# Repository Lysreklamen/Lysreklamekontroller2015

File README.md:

# Lysreklamekontroller2015
Modulært design

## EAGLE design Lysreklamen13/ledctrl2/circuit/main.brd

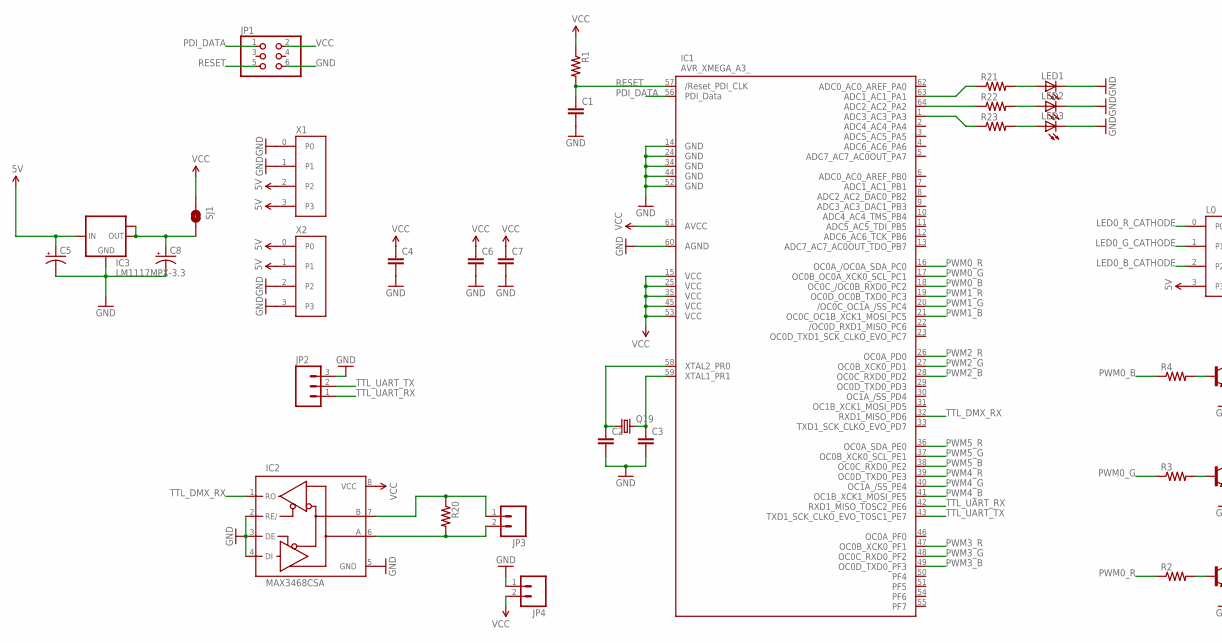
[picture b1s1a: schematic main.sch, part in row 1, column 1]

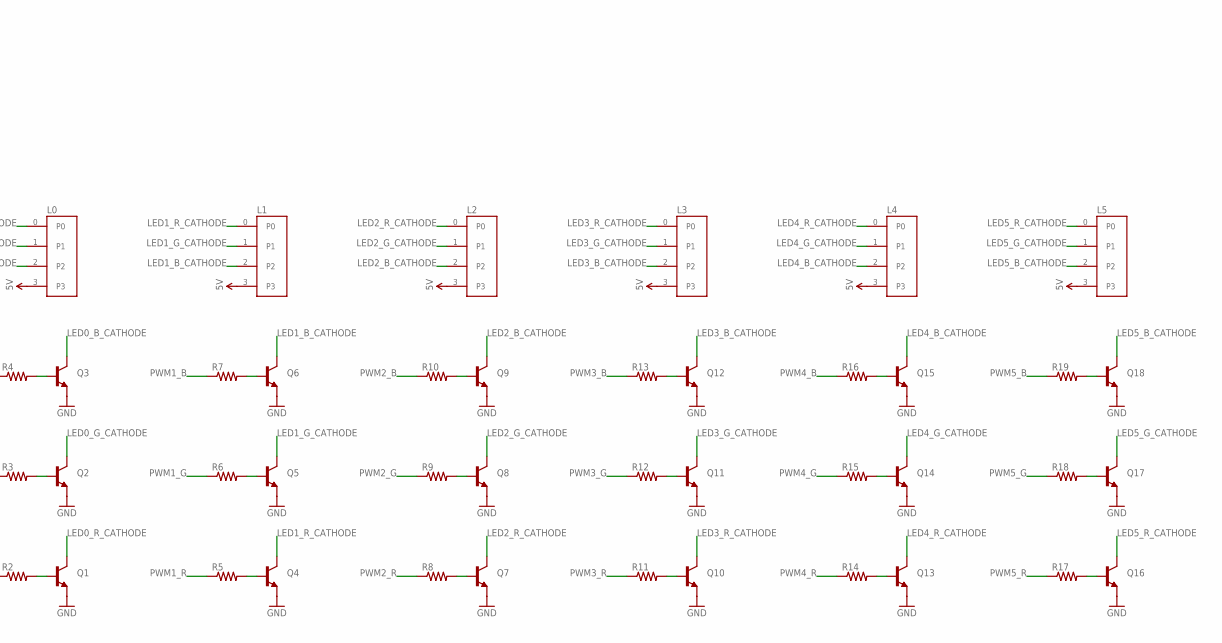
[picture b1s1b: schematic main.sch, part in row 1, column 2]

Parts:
C1, C2, C3, C4, C6, C7: CAP0805; 0805
C5, C8: CAP_POLSMD; VISHAY_C
IC1: AVR_XMEGA_A3_; TQFP64
IC2: MAX3468CSA; SO08
IC3: LM1117MPX-3.3; SOT223
JP1: PINHD-2X3; 2X03
JP2: M03LOCK_LONGPADS; 1X03_LOCK_LONGPADS
JP3, JP4: M02; 1X02_LONGPADS
L0, L1, L2, L3, L4, L5: SCREW-TERMINAL-4P; SK-CZZ-4P
LED1, LED2, LED3: LEDCHIPLED_0805; CHIPLED_0805
Q1, Q2, Q3, Q4, Q5, Q6, Q7, Q8, Q9, Q10, Q11, Q12, Q13, Q14, Q15, Q16, Q17, Q18: TRANSISTOR_NPNSOT89; SOT89
Q19: CRYSTALHC49UP; HC49UP
R1, R2, R3, R4, R5, R6, R7, R8, R9, R10, R11, R12, R13, R14, R15, R16, R17, R18, R19, R20, R21, R22, R23: RESISTOR; 0805
SJ1: SOLDERJUMPERNO; SJ_2S-NO
X1, X2: SCREW-TERMINAL-4P; SK-CZZ-4P

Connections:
5V: C5.+, IC3.3 (IN), L0.3, L1.3, L2.3, L3.3, L4.3, L5.3, X1.2, X1.3, X2.0, X2.1
GND: C1.2, C2.2, C3.2, C4.2, C5.-, C6.2, C7.2, C8.-, IC1.14 (GND1), IC1.24 (GND2), IC1.34 (GND3), IC1.44 (GND4), IC1.52 (GND5), IC1.60 (AGND), IC2.2 (RE/), IC2.3 (DE), IC2.4 (DI), IC2.5 (GND), IC3.1 (GND), JP1.6, JP2.3, JP4.1, LED1.C, LED2.C, LED3.C, Q1.3 (E), Q2.3 (E), Q3.3 (E), Q4.3 (E), Q5.3 (E), Q6.3 (E), Q7.3 (E), Q8.3 (E), Q9.3 (E), Q10.3 (E), Q11.3 (E), Q12.3 (E), Q13.3 (E), Q14.3 (E), Q15.3 (E), Q16.3 (E), Q17.3 (E), Q18.3 (E), X1.0, X1.1, X2.2, X2.3
LED0_B_CATHODE: L0.2, Q3.2 (C)
LED0_G_CATHODE: L0.1, Q2.2 (C)
LED0_R_CATHODE: L0.0, Q1.2 (C)
LED1_B_CATHODE: L1.2, Q6.2 (C)
LED1_G_CATHODE: L1.1, Q5.2 (C)
LED1_R_CATHODE: L1.0, Q4.2 (C)
LED2_B_CATHODE: L2.2, Q9.2 (C)
LED2_G_CATHODE: L2.1, Q8.2 (C)
LED2_R_CATHODE: L2.0, Q7.2 (C)
LED3_B_CATHODE: L3.2, Q12.2 (C)
LED3_G_CATHODE: L3.1, Q11.2 (C)
LED3_R_CATHODE: L3.0, Q10.2 (C)
LED4_B_CATHODE: L4.2, Q15.2 (C)
LED4_G_CATHODE: L4.1, Q14.2 (C)
LED4_R_CATHODE: L4.0, Q13.2 (C)
LED5_B_CATHODE: L5.2, Q18.2 (C)
LED5_G_CATHODE: L5.1, Q17.2 (C)
LED5_R_CATHODE: L5.0, Q16.2 (C)
unnamed: Q1.1 (B), R2.2
unnamed: Q2.1 (B), R3.2
unnamed: Q3.1 (B), R4.2
unnamed: Q4.1 (B), R5.2
unnamed: Q5.1 (B), R6.2
unnamed: Q6.1 (B), R7.2
unnamed: Q7.1 (B), R8.2
unnamed: Q8.1 (B), R9.2
unnamed: Q9.1 (B), R10.2
unnamed: Q10.1 (B), R11.2
unnamed: Q11.1 (B), R12.2
unnamed: Q12.1 (B), R13.2
unnamed: Q13.1 (B), R14.2
unnamed: Q14.1 (B), R15.2
unnamed: Q15.1 (B), R16.2
unnamed: Q16.1 (B), R17.2
unnamed: Q17.1 (B), R18.2
unnamed: Q18.1 (B), R19.2
unnamed: C2.1, IC1.58 (PR0), Q19.1
unnamed: C3.1, IC1.59 (PR1), Q19.2
unnamed: IC2.7 (B), JP3.1, R20.1
unnamed: IC2.6 (A), JP3.2, R20.2
unnamed: IC1.63 (PA1), R21.1
unnamed: C8.+, IC3.2 (OUT), IC3.TAB (OUT1), SJ1.2
unnamed: IC1.64 (PA2), R22.1
unnamed: IC1.1 (PA3), R23.1
unnamed: LED1.A, R21.2
unnamed: LED2.A, R22.2
unnamed: LED3.A, R23.2
PDI_DATA: IC1.56 (PDI_DATA), JP1.1
PWM0_B: IC1.18 (PC2), R4.1
PWM0_G: IC1.17 (PC1), R3.1
PWM0_R: IC1.16 (PC0), R2.1
PWM1_B: IC1.21 (PC5), R7.1
PWM1_G: IC1.20 (PC4), R6.1
PWM1_R: IC1.19 (PC3), R5.1
PWM2_B: IC1.28 (PD2), R10.1
PWM2_G: IC1.27 (PD1), R9.1
PWM2_R: IC1.26 (PD0), R8.1
PWM3_B: IC1.49 (PF3), R13.1
PWM3_G: IC1.48 (PF2), R12.1
PWM3_R: IC1.47 (PF1), R11.1
PWM4_B: IC1.41 (PE5), R16.1
PWM4_G: IC1.40 (PE4), R15.1
PWM4_R: IC1.39 (PE3), R14.1
PWM5_B: IC1.38 (PE2), R19.1
PWM5_G: IC1.37 (PE1), R18.1
PWM5_R: IC1.36 (PE0), R17.1
RESET: C1.1, IC1.57 (RESET), JP1.5, R1.2
TTL_DMX_RX: IC1.32 (PD6), IC2.1 (RO)
TTL_UART_RX: IC1.42 (PE6), JP2.1
TTL_UART_TX: IC1.43 (PE7), JP2.2
VCC: C4.1, C6.1, C7.1, IC1.15 (VCC1), IC1.25 (VCC2), IC1.35 (VCC3), IC1.45 (VCC4), IC1.53 (VCC5), IC1.61 (AVCC), IC2.8 (VCC), JP1.2, JP4.2, R1.1, SJ1.1

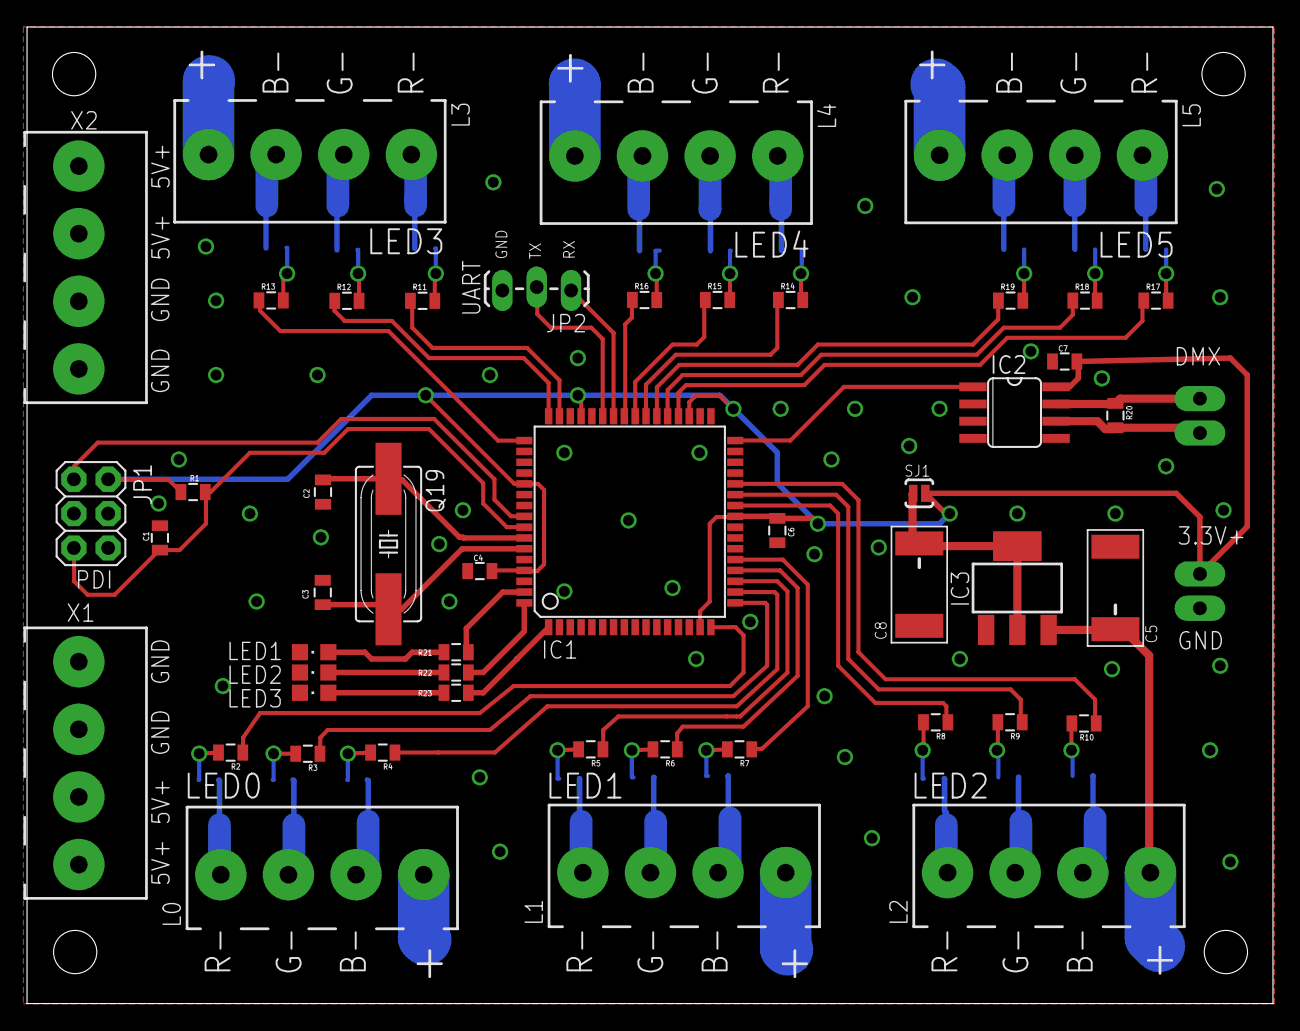
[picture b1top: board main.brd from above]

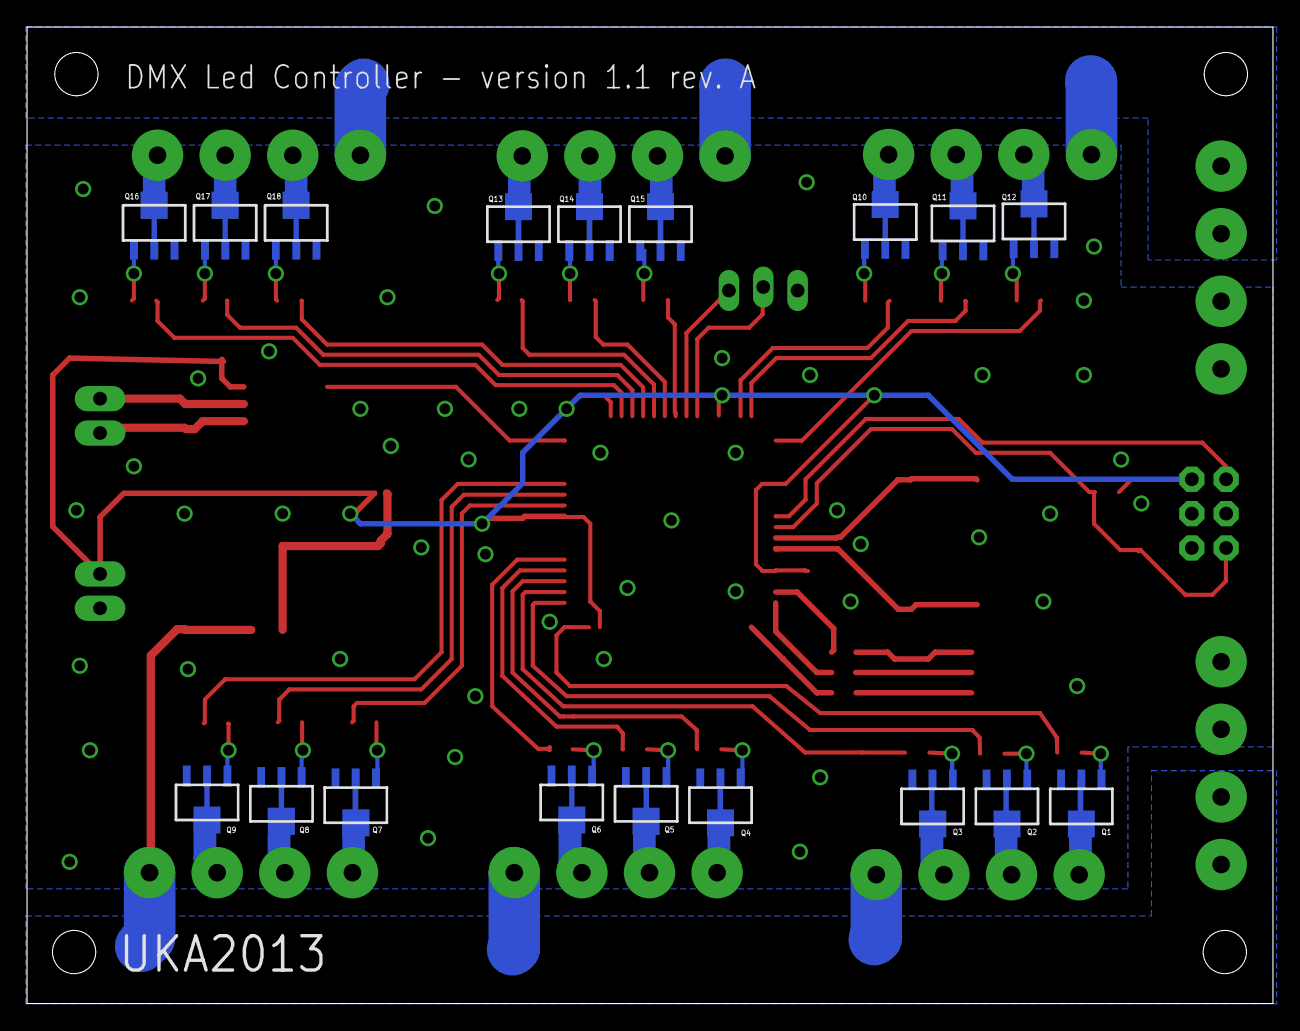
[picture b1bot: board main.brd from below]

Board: 2 copper layers, 92.1 x 72.2 mm, 69 parts (18 on the bottom side), 73 nets.

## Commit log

2015-02-05 Laget altiumprosjekt. Definert kortstørrelser
2015-02-05 Lagret alle dokumenter
2015-02-19 Laget LED holder, panelisert og generert gerber til seeed
2015-03-12 lysreklamen13-hardware
2015-04-12 jobbet med utlegg på bokskort
2015-05-07 Laget gerber fra riktig pcbfil (og zippet)
2015-05-07 Jobbet med skjematikk
2015-05-20 add component
2015-05-20 Nok en gang, panel-zip til seeed er generert.
2015-05-21 Lagt til board outline, generert gerber og zippet et enkelt LED-Holder kort
2015-05-21 Lagret prosjektfilen
2015-05-21 Jobbet på Kontrollerkort skjematikk
2015-06-04 Fikset mikrokontrollerkomponenten, etset kort for å teste konnektorer og plass i boks
2015-06-11 Lagt ut Kontrollerkort
2015-07-03 Fikset litt silk og generert output og pdf
2015-07-03 Gjort klart for review
2015-07-06 Lagd hunnkjønnsversjon av Lysreklameparalellbusskontakt2015 Gjort ferdig førsteutkast av Driverkort.PcbDoc
2015-07-16 Rutet ferdig
2015-07-16 Kontrollerkort er nå 6mm smalere
2015-07-23 Fikset ting nevnt i review Klart for final (hopefully) review
2015-07-23 Fikset boardoutline
2015-07-23 Laget bokskort minilysreklamen
2015-07-30 Generert gerbers og bestillt fra seedstudio
2015-09-14 Økt hullstørrelser på bokskort
2015-09-25 defaults + nytt defaultsystem
2015-09-25 fikset cardconf-idiotfeil
2015-09-25 added card 0-2 hex files
2015-09-25 added hexfiles 4-14
2015-09-25 updated dmx.c fra 13
2015-09-25 hex without ramdom på boks 4
2015-09-25 new hex 14-12
2015-09-25 hexfiles for 12-1 lagt til
2015-09-25 fix to defaults
2015-09-25 2 and 3 bacground changed
2017-03-17 fixed issue1 and generated BOM and output files
2017-03-18 added BOM to output files
2017-04-27 closes #1 and generated output files
2017-08-14 added board outline for kontrollerkort in layer mechanical2
2017-08-20 added gerber output for kontrollerkort
2017-10-01 update box 1
2017-10-01 add confs
2017-10-01 argf
2017-10-01 actually, correct hex
2017-11-12 jegtroddejeghaddepushetdenneijuli
2019-06-26 Kopiert til Lysreklamekontroller2013 repo
2019-06-26 Kopiert til Nedtellingsskilt2017 repo
2023-09-16 ting som burde vært commitet for flere år siden
2023-10-20 Default pattern 2023
2025-08-15 Skrudde ned klokkefrekvens for å fungere med rc filter
2025-08-15 fix stdlib i com.c, "how did this ever work"
2025-08-15 Rett type include
2025-08-15 slett ~85% av makefilen og så kommenter litt på den
2025-08-15 125kHz pdi
2025-08-16 Rydd og kommenter dmx-driveren
2025-08-16 Rydd i main
2025-08-16 Fjern masse kode vi ikke bruker
2025-09-22 Prøv å rydde i tilstandsmaskinen til dmx-handeren
2025-09-22 også legg til defaultframe
2025-09-22 småfix
2025-09-22 fix xmega_clock
2025-09-24 for-sikkerhets-skyld
2025-09-25 flake for avr development
2025-09-25 add more boxes
2025-09-27 Ny boksid og default virker
2025-09-27 Fiks en serie med off-by-one og gjør boksid-endringene relative
2025-09-27 Slett masse gamle cardconf
2025-09-27 slett alle de gamle hex-filene
